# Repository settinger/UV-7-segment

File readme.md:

# FR-4 Fluorescence Demo and 7-Segment Display PCB

## Intro

If you've ever played with a blacklight (or watched certain police procedurals), you've probably noticed that lots of materials fluoresce under a blacklight. However, one material I did *not* expect to fluoresce was FR-4, the common core material for PCBs. It emits a blue-green that you don't see in LEDs, it's more like old VFDs or strontium aluminate. You'll only see it on areas without soldermask, like the lines in-between boards on these panels:

So what's going on here? I have been making (and talking about) PCBs for over a decade, and I had never heard of this happening until I noticed it for myself! Is this common knowledge? Do people know about this and just don't care?

Well, if it's not common knowledge yet, I'd like to at least spread it around. Maybe someday, someone will remember this little fact and incorporate it into a beautiful work of art.

## The demo board

To demonstrate the phenomenon more clearly, I put together a 7-segment display PCB. The segments have had soldermask removed on both sides, and an 0805 UV LED is soldered upside-down under each segment. The pinout matches that of [common 7-segment modules](https://www.sparkfun.com/products/8546), but the rows of pins are 0.1 inches farther apart on mine, and external resistors are not needed on mine.

The plated slots between the segments stop light from bleeding through to neighboring segments. I haven't experimented much with them, maybe they can be shorter. They do need to be plated, though; if the walls of the slot are exposed, they will fluoresce! Defeating the entire point of the slots.

For this demo, the display is being driven by an Arduino. Each segment draws about 15 mA which the digital ports can handle just fine.

If you wanted to, you could put any color LEDs on this board. I don't see why not!

## Questions

After going through all this, I think I'm left with more questions than I started with! For one thing, why is the color so different on different PCBs? Let's compare the segments' colors on the Revision 2 PCB (1.6mm thick, made about a month ago) and the Revision 3 PCB (0.8mm thick, made this week).

In the picture above, you see that Rev 3 is so much brighter than Rev 2 when illuminated from above. Why? I don't think Rev 2 was this faint when I received it, but maybe it was?

In the picture above, both boards are lit from below. The Rev 2 board lights up quite well now! And it has the color I anticipated from the previous observations. The Rev 3 board has a much greener tint to it and I don't know why! Rev 3 is also brighter, which isn't too suprising since it's only 0.8mm thick. But when I dropped a second 0.8mm board on top of it, the resulting segments are even greener! It's more of a radium wristwatch color.

## Molecule talk

My unscientific hunch was that the fluorescence comes from bisphenol-A compounds used in the FR-4 epoxy to sandwich layers of fiberglass together. I *think* I read that BPA fluoresces. But what color? Do the other bisphenol analogues fluoresce?

The only PCB substrates that I *haven't* seen fluoresce are OSH Park's After Dark core (which is dyed black) and old boards that I think are FR-1 or FR-2. They might be G-10, I'm not sure how to check. But those also use BPA in their epoxy formulations, don't they? Like I said, I have more questions than when I started.

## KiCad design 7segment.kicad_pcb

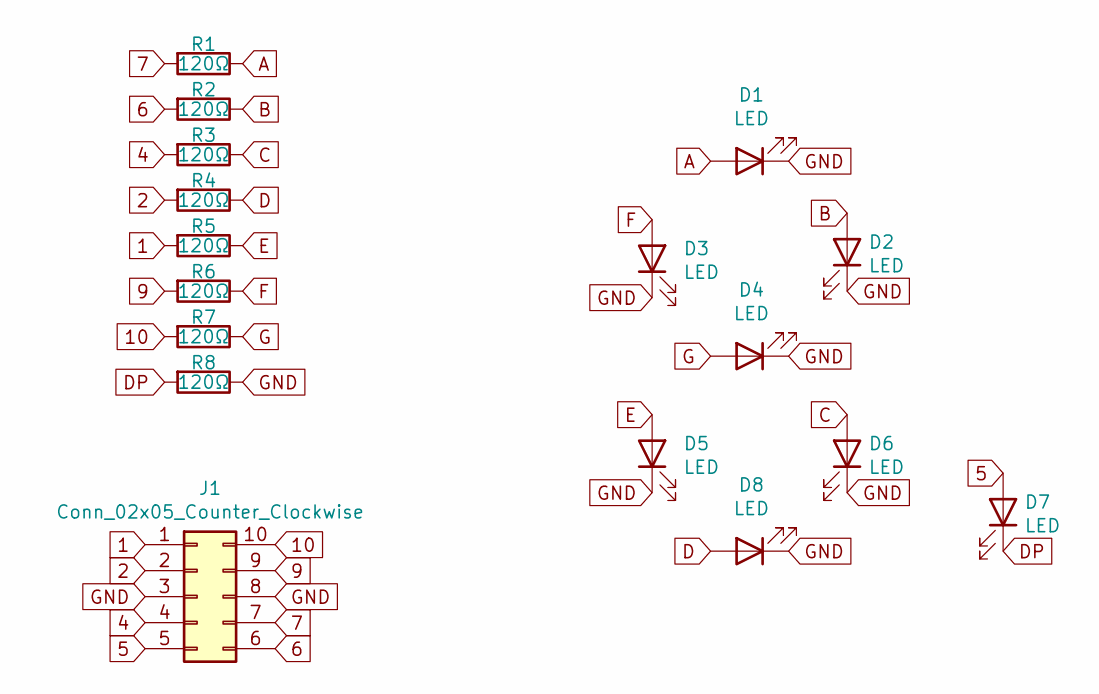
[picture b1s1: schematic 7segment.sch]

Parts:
D1, D2, D3, D4, D5, D6, D7, D8: LED; LED_0805_2012Metric_Pad1.15x1.40mm_HandSolder
J1: Conn_02x05_Counter_Clockwise; PinHeader_2x05_P2.54mm_Vertical
R1, R2, R3, R4, R5, R6, R7, R8: 120Ω; R_0805_2012Metric

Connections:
1: J1.1, R5.2
2: J1.2, R4.2
4: J1.4, R3.2
5: D7.2 (A), J1.5
6: J1.6, R2.2
7: J1.7, R1.2
9: J1.9, R6.2
10: J1.10, R7.2
A: D1.2 (A), R1.1
B: D2.2 (A), R2.1
C: D6.2 (A), R3.1
D: D8.2 (A), R4.1
DP: D7.1 (K), R8.2
E: D5.2 (A), R5.1
F: D3.2 (A), R6.1
G: D4.2 (A), R7.1
GND: D1.1 (K), D2.1 (K), D3.1 (K), D4.1 (K), D5.1 (K), D6.1 (K), D8.1 (K), J1.3, J1.8, R8.1

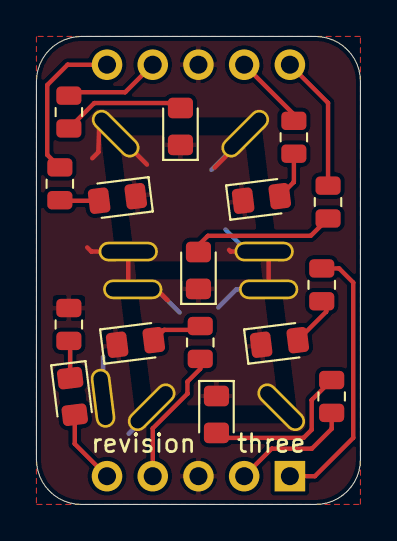
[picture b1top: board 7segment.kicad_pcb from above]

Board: 2 copper layers, 18.0 x 26.0 mm, 17 parts (1 on the bottom side), 17 nets.

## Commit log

2021-09-11 First version, has mistakes
2021-09-11 Maybe fixed?
2021-09-16 Revision 3, reverse-mount regular 0805 UV LEDs
2021-10-09 Ready to publish?
2021-10-09 Create LICENSE
2021-10-09 typo
